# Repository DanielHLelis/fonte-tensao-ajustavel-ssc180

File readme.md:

# Fonte de tensão ajustável 3V a 12V

Projeto de uma fonte de tensão ajustáve de 3V a 12V com corrente máxima 100mA.

Realizado para a disciplina de Eletrônica para Computação (SSC-0180) ministrado por Eduardo do Vale Simões.

## Projeto do circuito

O projeto começa pela definição dos componentes necessários para a construção do circuito. Nesse caso, podemos dividir o circuito
em quatro partes principais: transformação, retificação, filtragem e regulagem da tensão.

Ao longo do projeto, diversos componentes foram alterados para melhor cumprir os resultados necessários, desse modo, as decisões não seguem
necessariamente a ordem aqui estabelecida.

### Transformação

Dado que temos como tensão de entrada 127V RMS, precisaremos transformar essa tensão para um valor mais próximo ao nosso destino, para isso podemos utilizar um
transformador 127V/15V. Esse transformador nos proverar tensões de pico de aproximadamente 21,1V. Esse transformador foi escolhido pois
apresentava margem suficiente para as perdas que teremos mais a frente.

### Retificação

Agora que temos uma tensão mais próxima ao nosso destino, precisamos converter a corrente alternada para corrente contínua. Para isso, utilizaremos uma ponte de diodos.
Pelo uso da ponte de diodos no lugar de um retificador _full-wave_ (que foi impossibilitado pelo transformador a ser utilizado), teremos uma queda de tensão correspondente
a de dois diodos, ou seja, 1,4V.

### Filtragem

A fim de suavizar as oscilações de tensão após a retificação, precisaremos de realizar a filtragem. Para isso, podemos utilizar um capacitor que apresente capacitância suficiente para suportar a carga do circuito durante os períodos de queda na tensão. Quanto maior a capacidade do nosso capacitor, menor será o ripple, no caso, um ripple de no máximo 10% irá suprir com folga o circuito, já que, idealmente, ele não precisaria de mais de 14V, estando bem estável na faixa dos 16V. Além disso, dadas as estimativas de consumo que teremos (82,6 mA @ 19V), podemos calcular a resistência do circuito como, aproximadamente, 230 Ohms.

Calculando o capacitor mínimo para manter o ripple para até 14V dada resistência do circuito como 167 Ohms, teremos que ter, pelo menos, 344uF.

Sabendo que precisaremos de, no mínimo, 344uF, podemos obter um capacitor de 470uF para suportar a nossa carga, que irá nos dar um espaço ainda maior para carga e oscilações na entrada.

### Regulagem da tensão

Nesse ponto, temos uma tensão estável de entre 19V e 17V. Agora precisamos regulá-la para os valores desejados: de 3V a 12V suportando uma carga de até $100mA$. Para isso, utilizaremos um transistor (no caso, um par de transistores) para regular essa tensão entre os valores desejados. Para definirmos qual será o valor no dreno do transistor, utilizaremos um subcircuito que se conectará ao _gate_ do transistor. Esse subcircuito precisa apresentar uma tensão super estável para que tenhamos uma saída mais limpa possível. Por conta disso, utilizaremos um diodo zener em reverso com uma tensão de ruptura de 14V, utilizaremos, então um potenciômetro para alternar qual a tensão que teremos no _gate_ e, essa tensão, descartando a queda que teremos nos transistores, controlorá qual a tensão final do circuito.

Aqui, precisamos nos atentar a alguns pontos: primeiro, é importante que limitemos a corrente que chegará no sub-circuito que controlará o _gate_, a fim de evitar uma sobrecarga no zener. Para isso, podemos utilizar um resistor de 1k Ohms. Outro ponto importante é se atentar ao potencial de amplificação e as perdas que teremos no transistor. No caso, para conseguir a corrente necessária na saída com a corrente que teremos na saída do potenciômetro, precisaremos de dois transistores formando um par de Darlington, no caso, utilizaremos um pacote já com o par, o TIP120. No caso do potenciômetro, um de 10k Ohms seguido de dois resistores de 2.2k Ohms (aproximação para resistores comercialmente disponíveis), irá nos prover a corrente necessária para controlar os transistores sob a carga máxima no circuito, nos dando tensões a partir de 3V indo até 12,6V (por conta da queda de tensão nos dois transistores).

Estipulando os consumos teremos:

| Parte                  | Corrente máx. @19V |
| ---------------------- | :----------------: |
| Zener e Potentciômetro |       19 mA        |
| Perda nos Transistores |       0,5 mA       |
| Carga Máxima           |      63,1 mA       |
| **Total**              |    **82,6 mA**     |

## Componentes

| Componente                       | Quantidade |                                                                      Preço Un.                                                                      |
| -------------------------------- | :--------: | :-------------------------------------------------------------------------------------------------------------------------------------------------: |
| Transformador 127V/15V 500mA     |     1      |                                 [R\$27,99](https://www.soldafria.com.br/transformador-15v-500ma-entrada-110-220vac)                                 |
| Diodo 1N4007                     |     4      |          [R\$0,14](https://www.soldafria.com.br/componentes-eletronicos/diodo/diodo-1nxxxx/diodo-1n4007-retificador-de-uso-geral-1a-700v)           |
| Capacitor Eletrolítico 470uF 50V |     1      | [R\$1,06](https://www.soldafria.com.br/componentes-eletronicos/capacitor/capacitor-eletrolitico-50v/capacitor-eletrolitico-470uf-x-50v-p-1866.html) |
| Potenciômetro 10K Logarítmico    |     1      |                                    [R\$1,91](https://www.soldafria.com.br/potenciometro-logaritmo-mini-10ka-l15)                                    |
| Diodo Zener 14V 5W               |     1      |                                    [R\$1,07](https://www.soldafria.com.br/diodo-zener-14v-5w-1n5351-p-7621.html)                                    |
| Transistor TIP120                |     1      |                                        [R\$1,83](https://www.soldafria.com.br/transistor-tip120-p-1384.html)                                        |
| Resistor 2K2 1/4W                |     2      |                                 [R\$0,13](https://www.soldafria.com.br/resistor-de-2k2-carbono-5-1-4w-vm-vm-vm-dr)                                  |
| Resistor 1K 1W                   |     1      |                                    [R\$0,18](https://www.soldafria.com.br/resistor-1k-5-1w-mrptvmdr-p-4731.html)                                    |

## Simulação

Segue a simulação do circuito no falstad: [link](http://falstad.com/circuit/circuitjs.html?ctz=CQAgjCAMB0l3BWEAmM0EE4DMGAcB2ZLMSANjABYxkQKsQk6GBTAWjDACgA3EV0iuGp8BILFlJRwIUpHC45iqOk4AVMTQ40Mk8ZLmCYYeqxjJzO4xXwJkuCZQisE6BBzBui1BPntsw+MoYwZwA7iKCWhpCNJBhEWIS0XpQ8Tox4LIZceHpKWBZKXEAJplyKeaRwjTFzABmAIYArgA2AC6cpQVyUZUZNfXN7Z0ohImS3eMoILWNrR2lyGP5Wb0zg-PxSzQpWLZTOWL7URSiUYd7O0mngkVbyFU7x8JxAE4MwlGeKJC4UiRweI3DLfc5A0Qpb53NoMDCaLKkB5lf58ALQUgY2ykcRkfDEGzKBCkPCQIgPciQBB7aKzIYdGGIwR9UhElBInqo3DQIjYuws2z2fAQGAY0k4CgYNxC4wYGkbYbhRngfCSJV9Q5KyiCFkTCiGeI68B6mSs5C-VLhUHCTUvTgBQQCn5-HySM1-CAAuBBSXwX1+iAAJWYAGcAJbBtoNAB2AGNmPFvm6GHYnRaPldJJgM2miT04QxVllDrnkVnkRqkVFNcaNaaKHJDchWcX8ylDXdFay212zaksIIAF7MKPMV7sSLgaBCugCsBw3Ce5BsQJyZCwBR+zeyyjgTgD9NTRP16ZDkdjygJ6rHxPmt6wmhJsvbKTmQHvJ9jMtFNmAzuu1n4JATLNgaPZyIBty9neuAUH8fQwX8WBAf8gIFDQCFiMhGGXNMtLzKwLTMF0UiKLAXDhIQq5IhBKAgeE2H7JRRyxPENFYL2TE4YcTF9L4TLsqxMFsoIGHqpwZqyjhUQ4d+MDwNYKBoDocC4FSAiQMQ5jSFwADmozZs+Eh-IonAAPa0Nqhi0HsSBNtAc4SEKCBAYB+ASrE9mUgoMF7KSsGkj4L4WWIIAADKmQ0xScEAA)

## Esquemático e PCB

Ambos diagramas do esquemático e da PCB foram feitos no EAGLE e estão disponíveis aqui no repositório.

No caso dos conectores utilizados na PCB, temos dois _MTA02-100_, um para entrada, outro para saída, sendo escolhido pelo baixo custo e apresentar capacidade dentro dos limites do circuito.

### Esquemático

### PCB

## Vídeo explicativo

[Não tão breve descrição do circuito e decisões que o cercaram](https://youtu.be/d2nFDi0Lc-U)

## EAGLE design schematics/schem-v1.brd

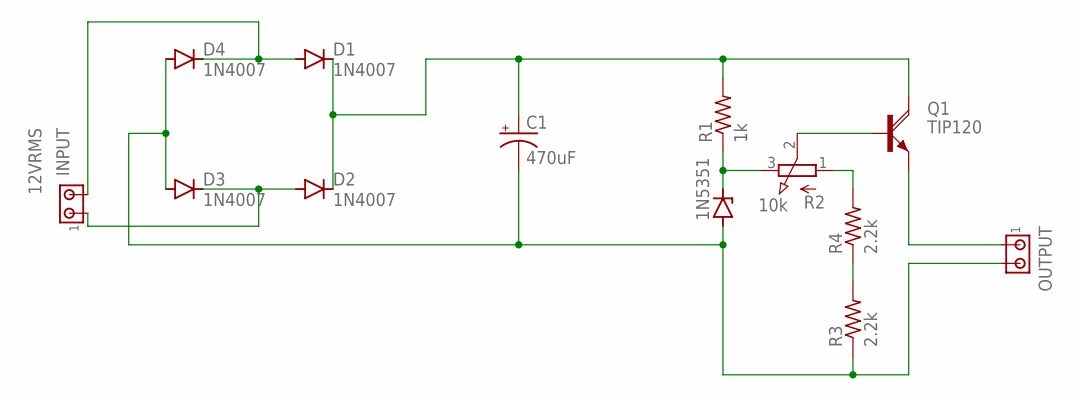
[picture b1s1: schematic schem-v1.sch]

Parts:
1N5351: ZENER-DIODEDO41Z10; DO41Z10
C1: 470uF; E3,5-10
D1, D2, D3, D4: 1N4007; DO41-10
INPUT: 12VRMS; 10X02MTA
OUTPUT: MTA02-100; 10X02MTA
Q1: TIP120; TO220AH
R1: 1k; 0207/10
R2: 10k; 3RP/1610N
R3, R4: 2.2k; 0207/10

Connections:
GND: 1N5351.A, C1.-, D3.A, D4.A, OUTPUT.2, R3.1
unnamed: D1.A, D4.C, INPUT.2
unnamed: D2.A, D3.C, INPUT.1
unnamed: 1N5351.C, R1.1, R2.3 (E)
unnamed: R2.1 (A), R4.2
unnamed: R3.2, R4.1
unnamed: Q1.B, R2.2 (S)
unnamed: OUTPUT.1, Q1.E
VCC: C1.+, D1.C, D2.C, Q1.C, R1.2

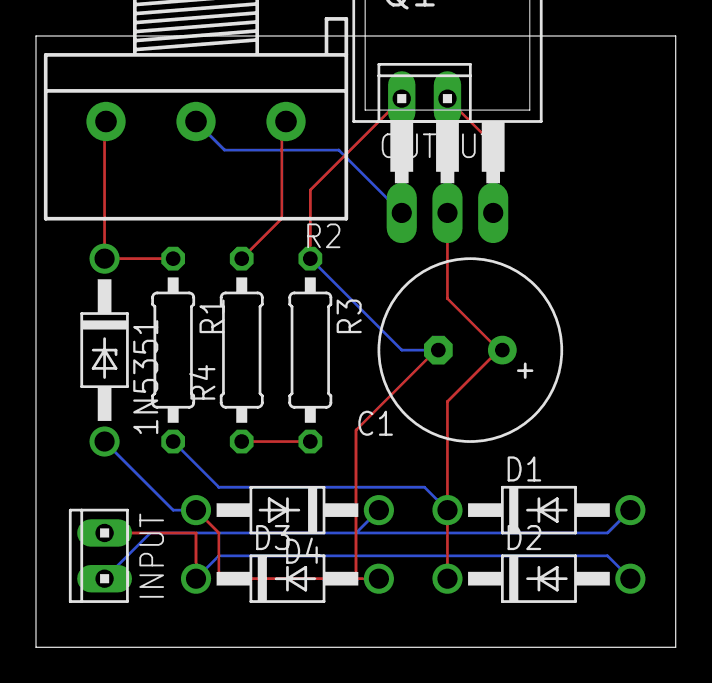
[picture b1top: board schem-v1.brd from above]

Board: 2 copper layers, 35.5 x 34.0 mm, 13 parts (0 on the bottom side), 9 nets.

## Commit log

2021-07-28 power supply first iteration
2021-07-29 second iteration: transformer adjustments
2021-07-29 added video and new gif
2021-07-29 PCB layout update
